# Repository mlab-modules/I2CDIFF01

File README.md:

# I2CDIFF01 - Differential I²C Transceiver

Allows long-range I²C communication in harsh environments. In addition to I²C data transfer, the module supports bidirectional interrupt signaling over the same cable.

## Features

* Converts standard I²C signals to differential I²C for robust transmission
* Supports interrupt signal transmission
* Uses PCA9616 buffer for differential I²C communication
* Enables power transmission over RJ45 cable
* Configurable voltage levels using onboard jumpers
* Power regulation with onboard voltage regulators
* RJ45 (Ethernet) cable for differential connection (UTP cable compatible)

## Technical Specifications

| Parameter      | Value                 |
| -------------- | --------------------- |
| Supply Voltage | Up to 15 V            |
| Communication  | I²C, Differential I²C |
| Main IC        | PCA9616               |
| Dimensions     | 40.1 × 50.3 × 16 mm   |

## Power and Voltage Configuration

* **VDDA**: Voltage for single-ended I²C side (selectable 3.3 V or 5 V by jumper; replace regulator for other voltages)
* **VDDB**: Voltage for differential I²C side (recommended 5 V)
* Power is supplied via the RJ45 cable; only one module in the chain should provide power
* Optional jumper on EXT-VDD allows routing of input voltage to internal regulator if below 15 V

## Connector Use

* **RJ45 connector** used for differential I²C transmission and power
* Do not connect the RJ45 cable to standard Ethernet equipment

## Jumpers and Configuration

* Jumpers available to select voltage sources (VDD1 or VDD2) for VDDA and VDDB
* Recommended not to use the SEL jumper when VDDA > 2.2 V
* Voltage levels indicated on PCB; use permanent marker to label used levels

## Typical Use Cases

* Extending I²C bus over longer distances
* Connecting devices across electrically noisy environments
* Applications requiring shared interrupt signaling across modules

## Notes

* Ensure proper termination of differential pairs per PCA9616 datasheet
* Verify jumper settings and supply voltages before powering the module
* Do not mix power sources across RJ45-connected modules

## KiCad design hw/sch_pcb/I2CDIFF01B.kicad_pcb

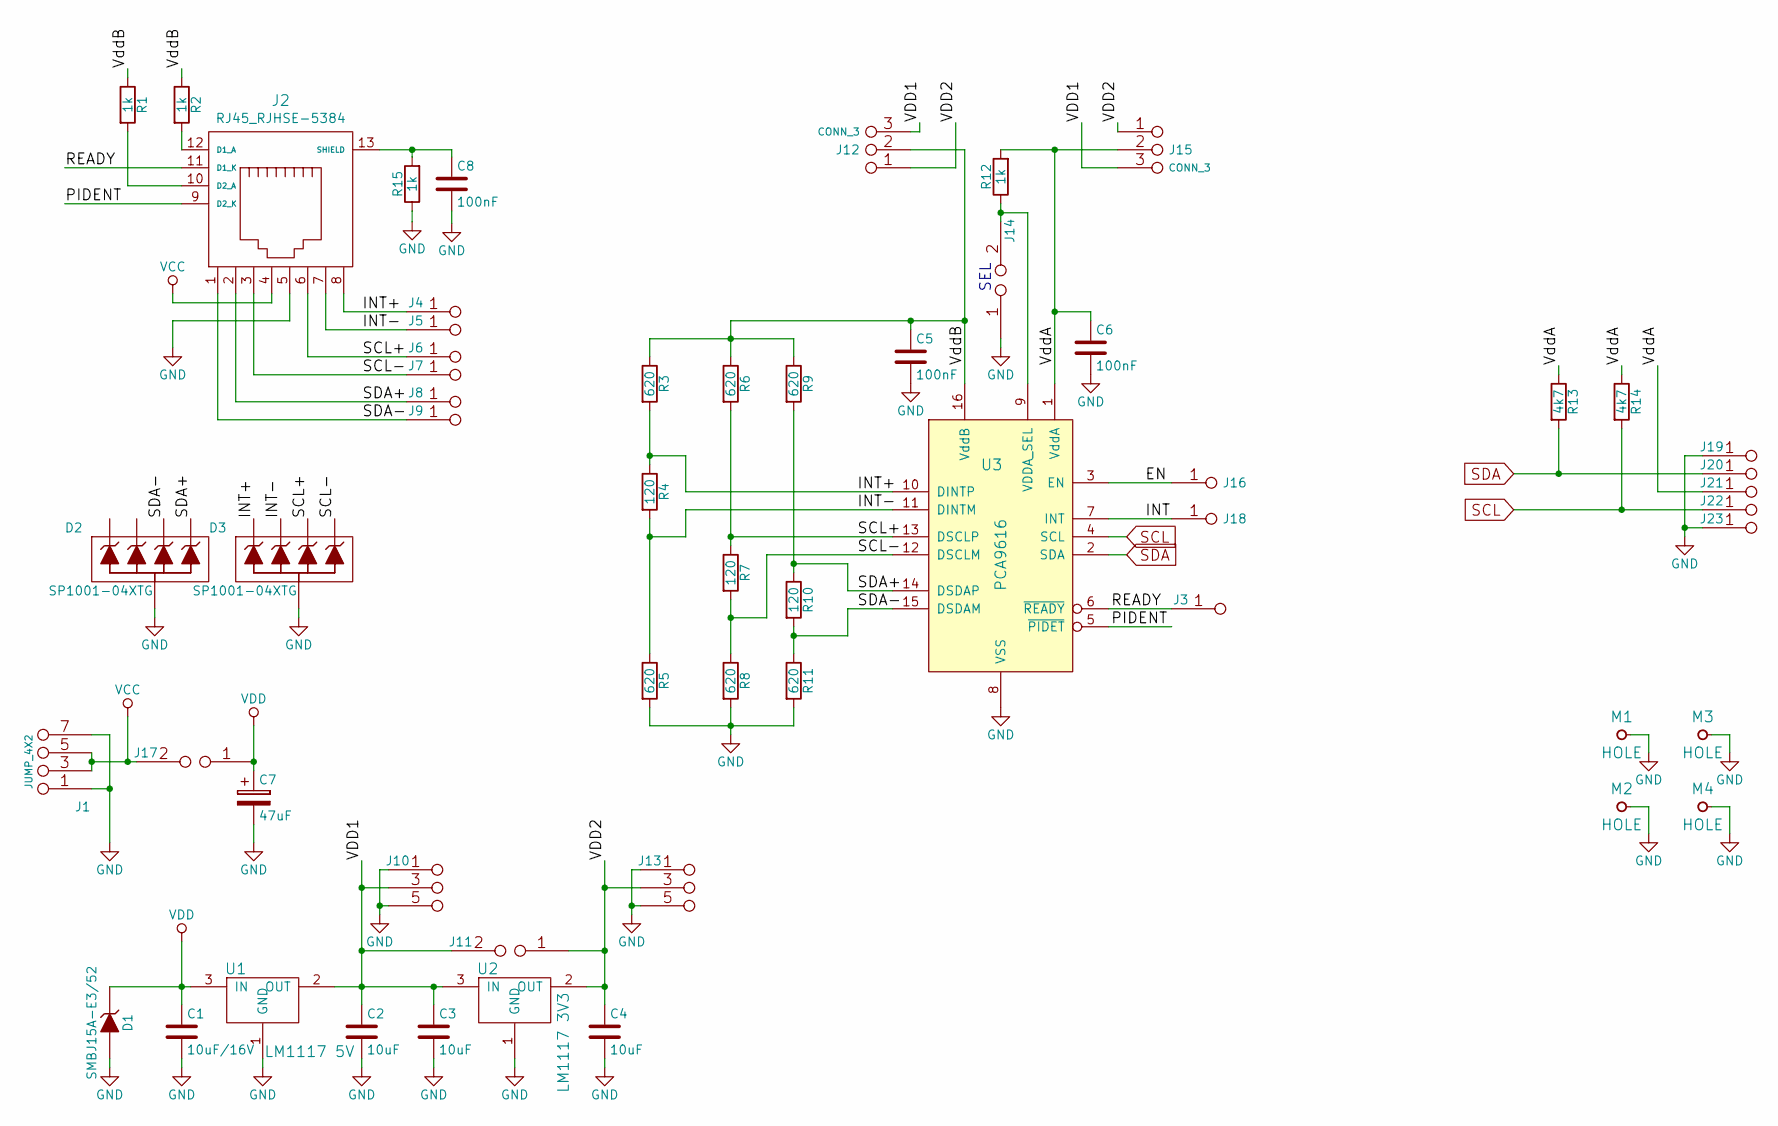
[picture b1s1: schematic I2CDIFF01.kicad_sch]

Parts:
C1: 10uF/16V; SMD-0805
C2, C3, C4: 10uF; SMD-0805
C5, C6, C8: 100nF; SMD-0805
C7: 47uF; TantalC_SizeC_Reflow
D1: SMBJ15A-E3/52; Diode-SMB_Standard
D2, D3: SP1001-04XTG; SOT-553
J1: JUMP_4X2; Straight_2x04
J2: RJ45_RJHSE-5384; RJHSE-5384(RJ45)
J3, J19, J20, J21, J22, J23: JUMP_2x1; Straight_1x02
J4, J5, J6, J7, J8, J9: JUMP_2x1; Straight_2x01
J10, J13: JUMP_3X2; Straight_2x03
J11, J14, J17: JUMP2_2x1; Straight_2x01
J12, J15: CONN_3; Straight_1x03
J16, J18: CONN1_1; Straight_1x01
M1, M2, M3, M4: HOLE; MountingHole_3mm
R1, R2, R12, R15: 1k; SMD-0805
R3, R5, R6, R8, R9, R11: 620; SMD-0805
R4, R7, R10: 120; SMD-0805
R13, R14: 4k7; SMD-0805
U1: LM1117 5V; SOT-223
U2: LM1117 3V3; SOT-223
U3: PCA9616; TSSOP-16_4.4x5mm_Pitch0.65mm

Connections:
/EN: J16.1, U3.3 (EN)
/INT: J18.1, U3.7 (INT)
/INT+: D3.1, J2.8, J4.1, J4.2, R3.2, R4.1, U3.10 (DINTP)
/INT-: D3.3, J2.7, J5.1, J5.2, R4.2, R5.1, U3.11 (DINTM)
/PIDENT: J2.9 (D2_K), U3.5 (~PIDET)
/READY: J2.11 (D1_K), J3.1, J3.2, U3.6 (~READY)
/SCL+: D3.4, J2.6, J6.1, J6.2, R6.2, R7.1, U3.13 (DSCLP)
/SCL-: D3.5, J2.3, J7.1, J7.2, R7.2, R8.1, U3.12 (DSCLM)
/SDA+: D2.5, J2.2, J8.1, J8.2, R9.2, R10.1, U3.14 (DSDAP)
/SDA-: D2.4, J2.1, J9.1, J9.2, R10.2, R11.1, U3.15 (DSDAM)
/VDD1: C2.1, C3.1, J10.3 (4), J10.4, J11.2, J12.3, J15.3, U1.2 (OUT), U1.4 (OUT), U2.3 (IN)
/VDD2: C4.1, J11.1, J12.1, J13.3 (4), J13.4, J15.1, U2.2 (OUT), U2.4 (OUT)
/VddA: C6.1, J15.2 (PM), J21.1, J21.2, R12.2, R13.1, R14.1, U3.1 (VddA)
/VddB: C5.1, J12.2 (PM), R1.1, R2.1, R3.1, R6.1, R9.1, U3.16 (VddB)
GND: C1.2, C2.2, C3.2, C4.2, C5.2, C6.2, C7.2, C8.2, D1.1 (A), D2.2, D3.2, J1.1 (2), J1.2, J1.7 (8), J1.8, J2.5, J10.1 (2), J10.2, J10.5 (6), J10.6, J13.1 (2), J13.2, J13.5 (6), J13.6, J14.1, J19.1, J19.2, J23.1, J23.2, M1.1, M2.1, M3.1, M4.1, R5.2, R8.2, R11.2, R15.1, U1.1 (GND), U2.1 (GND), U3.8 (VSS)
unnamed: C8.1, J2.13 (SHIELD), R15.2
unnamed: J2.10 (D2_A), R1.2
unnamed: J2.12 (D1_A), R2.2
unnamed: J14.2, R12.1, U3.9 (VDDA_SEL)
SCL: J22.1, J22.2, R14.2, U3.4 (SCL)
SDA: J20.1, J20.2, R13.2, U3.2 (SDA)
VCC: J1.3 (4), J1.4, J1.5, J1.6 (5), J2.4, J17.2
VDD: C1.1, C7.1, D1.2 (K), J17.1, U1.3 (IN)

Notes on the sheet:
SEL

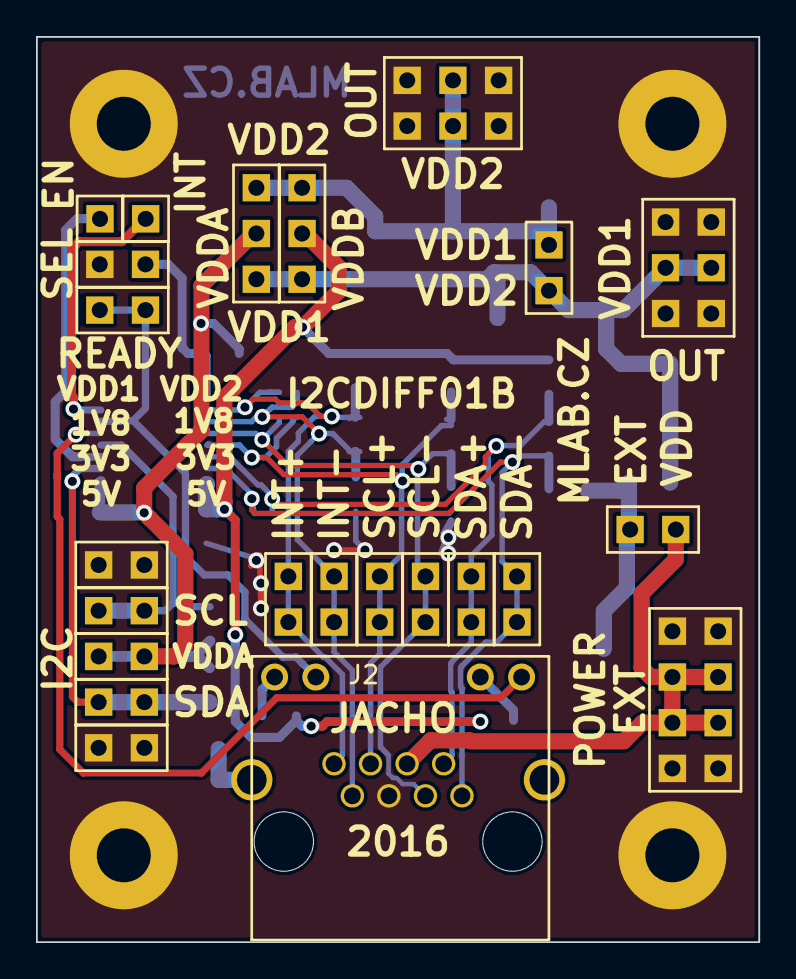
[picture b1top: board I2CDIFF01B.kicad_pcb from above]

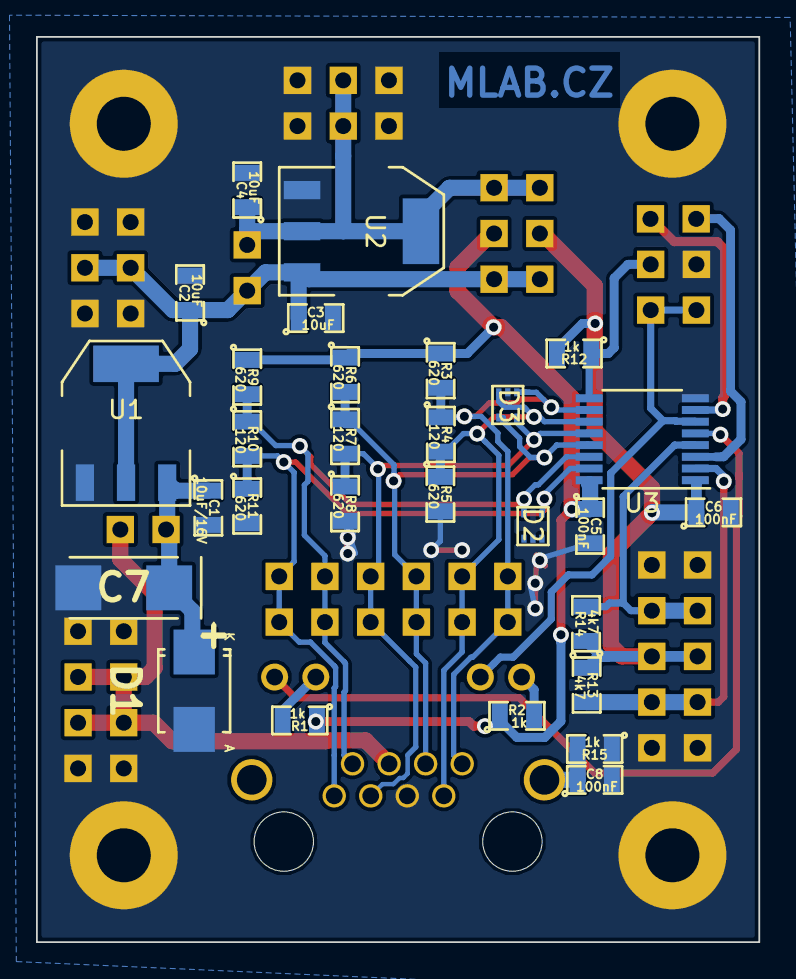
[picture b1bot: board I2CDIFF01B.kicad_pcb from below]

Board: 2 copper layers, 40.1 x 50.3 mm, 56 parts (29 on the bottom side), 23 nets.

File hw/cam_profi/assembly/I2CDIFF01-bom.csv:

Component,Description,Part,References,Value,Footprint,Quantity Per PCB,Datasheet
1,,C_9,C5,100nF,SMD-0805,1,
2,,C_8,C6,100nF,SMD-0805,1,
3,,C_10,C8,100nF,SMD-0805,1,
4,,C_12,C2,10uF,SMD-0805,1,
5,,C_13,C3,10uF,SMD-0805,1,
6,,C_14,C4,10uF,SMD-0805,1,
7,,CP_2,C7,47uF,TantalC_SizeC_Reflow,1,
8,,C_11,C1,10uF/16V,SMD-0805,1,
9,,D_ZENER_2,D1,SMBJ15A-E3/52,Diode-SMB_Standard,1,
10,,D_4xZENER_3,D2,SP1001-04XTG,SOT-553,1,
11,,D_4xZENER_4,D3,SP1001-04XTG,SOT-553,1,
12,,CONN1_1_3,J16,CONN1_1,Straight_1x01,1,
13,,CONN1_1_4,J18,CONN1_1,Straight_1x01,1,
14,,CONN_3_4,J12,CONN_3,Straight_1x03,1,
15,,CONN_3_3,J15,CONN_3,Straight_1x03,1,
16,,JUMP2_2x1_6,J11,JUMP2_2x1,Straight_2x01,1,
17,,JUMP2_2x1_4,J14,JUMP2_2x1,Straight_2x01,1,
18,,JUMP2_2x1_5,J17,JUMP2_2x1,Straight_2x01,1,
19,,JUMP_2x1_17,J19,JUMP_2x1,Straight_1x02,1,
20,,JUMP_2x1_15,J20,JUMP_2x1,Straight_1x02,1,
21,,JUMP_2x1_16,J21,JUMP_2x1,Straight_1x02,1,
22,,JUMP_2x1_18,J22,JUMP_2x1,Straight_1x02,1,
23,,JUMP_2x1_14,J23,JUMP_2x1,Straight_1x02,1,
24,,JUMP_2x1_13,J3,JUMP_2x1,Straight_1x02,1,
25,,JUMP_2x1_24,J4,JUMP_2x1,Straight_2x01,1,
26,,JUMP_2x1_19,J5,JUMP_2x1,Straight_2x01,1,
27,,JUMP_2x1_20,J6,JUMP_2x1,Straight_2x01,1,
28,,JUMP_2x1_21,J7,JUMP_2x1,Straight_2x01,1,
29,,JUMP_2x1_22,J8,JUMP_2x1,Straight_2x01,1,
30,,JUMP_2x1_23,J9,JUMP_2x1,Straight_2x01,1,
31,,JUMP_3X2_4,J10,JUMP_3X2,Straight_2x03,1,
32,,JUMP_3X2_3,J13,JUMP_3X2,Straight_2x03,1,
33,,JUMP_4X2_2,J1,JUMP_4X2,Straight_2x04,1,
34,,RJ45_RJHSE-5384_2,J2,RJ45_RJHSE-5384,RJHSE-5384(RJ45),1,
35,,R_24,R10,120,SMD-0805,1,
36,,R_26,R4,120,SMD-0805,1,
37,,R_21,R7,120,SMD-0805,1,
38,,R_23,R11,620,SMD-0805,1,
39,,R_27,R3,620,SMD-0805,1,
40,,R_25,R5,620,SMD-0805,1,
41,,R_18,R6,620,SMD-0805,1,
42,,R_22,R8,620,SMD-0805,1,
43,,R_17,R9,620,SMD-0805,1,
44,,R_29,R1,1k,SMD-0805,1,
45,,R_16,R12,1k,SMD-0805,1,
46,,R_30,R15,1k,SMD-0805,1,
47,,R_28,R2,1k,SMD-0805,1,
48,,R_19,R13,4k7,SMD-0805,1,
49,,R_20,R14,4k7,SMD-0805,1,
50,,LM1117_4,U2,LM1117 3V3,SOT-223,1,
51,,LM1117_3,U1,LM1117 5V,SOT-223,1,
52,,PCA9616_2,U3,PCA9616,TSSOP-16_4.4x5mm_Pitch0.65mm,1,

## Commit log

2023-04-01 Adding force option to enable splitting in not fresh copy of Modules repository.
2023-05-28 automated commit; add github actions
2023-05-28 Update workflow files
2023-05-28 Update metadata files
2023-07-05 automated commit; rename source files to new naming convence
2025-08-19 Update workflow and KiCAD project to v 9.
2025-08-19 Cleanup repository and KiCAD project.
2025-08-19 Update actions products
2025-08-19 Update documentation.
